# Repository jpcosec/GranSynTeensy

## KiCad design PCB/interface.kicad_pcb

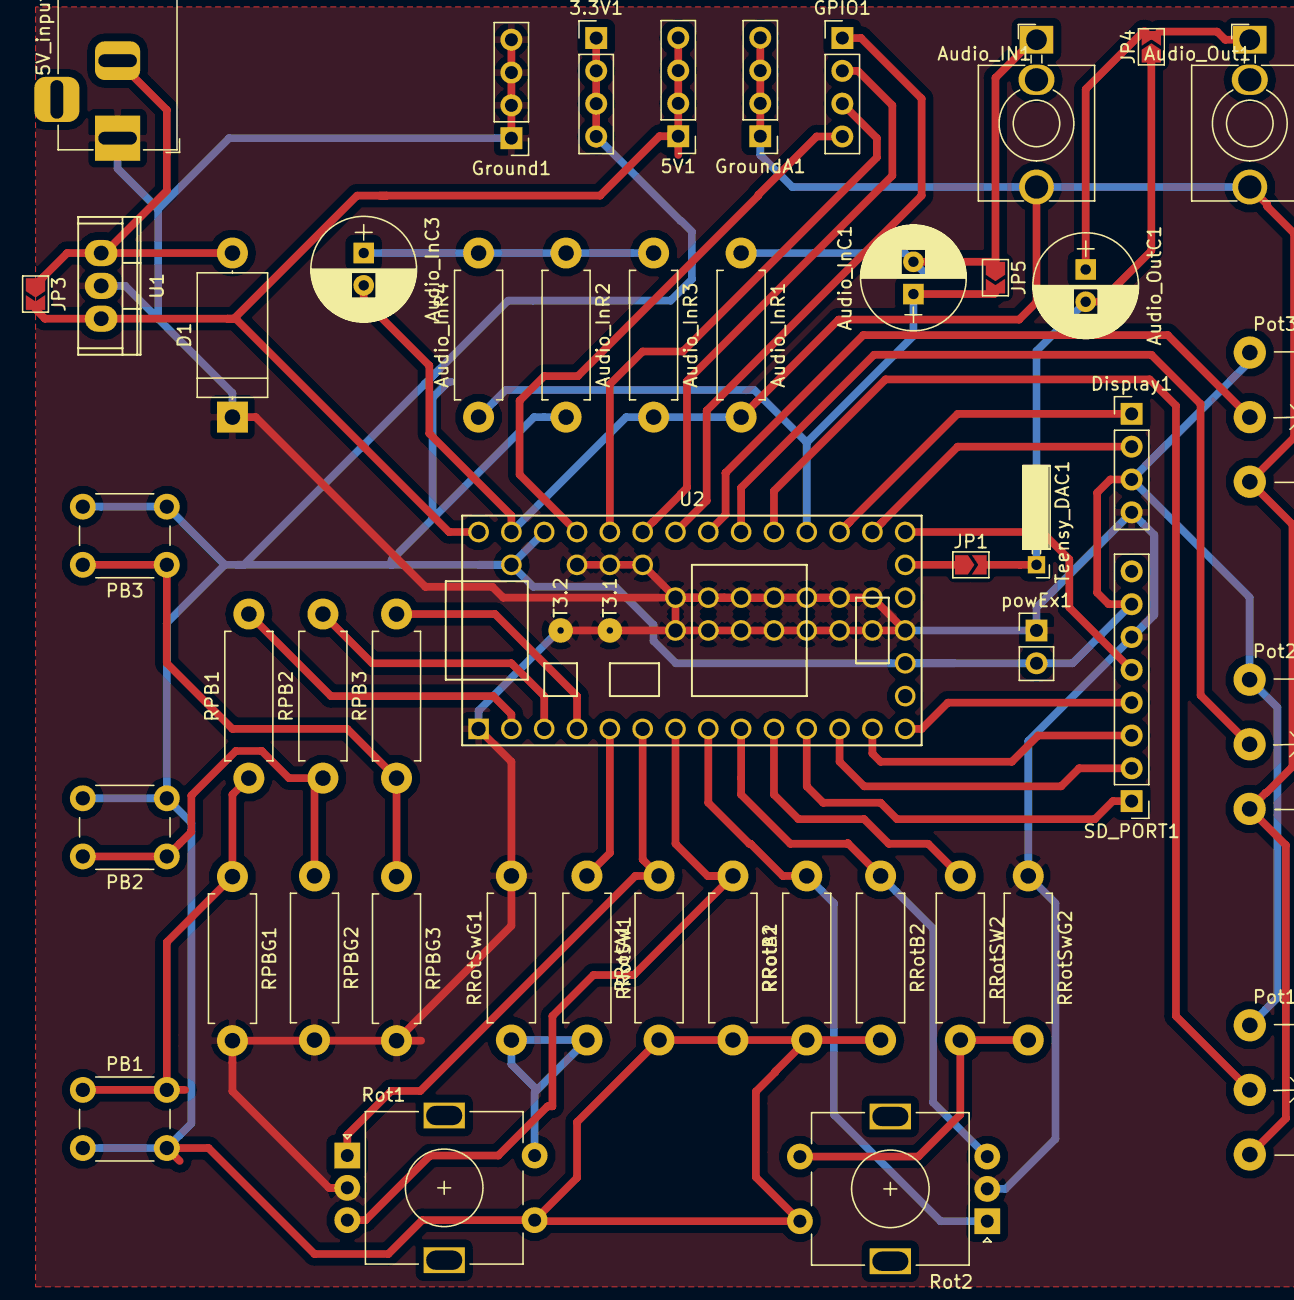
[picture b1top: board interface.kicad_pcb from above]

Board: 2 copper layers, 48 parts (0 on the bottom side), 39 nets.

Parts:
3.3V1, 5V1: Conn_01x04_Female; Pin_Header_Straight_1x04_Pitch2.54mm
5V_input1: Jack-DC; BarrelJack_Horizontal
Audio_IN1: AudioJack2_Ground; Jack_3.5mm_QingPu_WQP-PJ398SM_Vertical_CircularHoles
Audio_InC1, Audio_InC3: 10uf; CP_Radial_D8.0mm_P2.50mm
Audio_InR1, Audio_InR4: 47K; R_Axial_DIN0411_L9.9mm_D3.6mm_P12.70mm_Horizontal
Audio_InR2: 10K; R_Axial_DIN0411_L9.9mm_D3.6mm_P12.70mm_Horizontal
Audio_InR3: 2.2K; R_Axial_DIN0411_L9.9mm_D3.6mm_P12.70mm_Horizontal
Audio_Out1: AudioJack2_Ground; Jack_3.5mm_QingPu_WQP-PJ398SM_Vertical_CircularHoles
Audio_OutC1: 10uf; CP_Radial_D8.0mm_P2.50mm
D1: DIODE; D_DO-27_P12.70mm_Horizontal
Display1: Conn_01x04_Female; Pin_Header_Straight_1x04_Pitch2.54mm
GPIO1: Conn_01x04_Female; Pin_Header_Straight_1x04_Pitch2.54mm
Ground1: Conn_01x04_Female; Pin_Header_Straight_1x04_Pitch2.54mm
GroundA1: Conn_01x04_Female; Pin_Header_Straight_1x04_Pitch2.54mm
JP1, JP3, JP4, JP5: Jumper_NO_Small; SolderJumper-2_P1.3mm_Open_TrianglePad1.0x1.5mm
PB1, PB2, PB3: SW_Push; SW_PUSH_6mm_h4.3mm
Pot1, Pot2, Pot3: R_POT; Potentiometer_WirePads_largePads
RPB1, RPB2, RPB3: 220R; R_Axial_DIN0411_L9.9mm_D3.6mm_P12.70mm_Horizontal
RPBG1, RPBG2, RPBG3: 10k; R_Axial_DIN0411_L9.9mm_D3.6mm_P12.70mm_Horizontal
RRotA1, RRotA2: 10k; R_Axial_DIN0411_L9.9mm_D3.6mm_P12.70mm_Horizontal
RRotB1, RRotB2: 10k; R_Axial_DIN0411_L9.9mm_D3.6mm_P12.70mm_Horizontal
RRotSW1, RRotSW2: 220R; R_Axial_DIN0411_L9.9mm_D3.6mm_P12.70mm_Horizontal
RRotSwG1, RRotSwG2: 10k; R_Axial_DIN0411_L9.9mm_D3.6mm_P12.70mm_Horizontal
Rot1, Rot2: Rotary; RotaryEncoder_Alps_EC11E-Switch_Vertical_H20mm
SD_PORT1: Conn_01x08_Female; Pin_Header_Straight_1x08_Pitch2.54mm
Teensy_DAC1: Conn_01x01_Female; Socket_Strip_Angled_1x01_Pitch2.00mm
U1: LM7805_TO220; TO-220
U2: Teensy3.2; Teensy30_31_32_LC
powEx1: Conn_01x02_Female; Pin_Header_Straight_1x02_Pitch2.54mm

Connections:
+3V3: 3.3V1.1, 3.3V1.2, 3.3V1.3, 3.3V1.4, Audio_InR2.2, Display1.3, PB1.2, PB2.2, PB3.2, Pot1.1, Pot2.1, Pot3.1, RRotA1.1, RRotA2.1, RRotB1.2, RRotB2.2, Rot1.S1, Rot2.S2, SD_PORT1.7, U2.16, U2.31, U2.34, powEx1.2
+5V: 5V1.1, 5V1.2, 5V1.3, 5V1.4, JP3.2, U1.3, U2.33
AUDIO_IN: Audio_InC1.1, Audio_InR4.1, JP5.2, U2.23
CLK_DISP: Display1.1, U2.22
CS: SD_PORT1.2, U2.12
CSK: SD_PORT1.5, U2.20
DAC: JP1.1, U2.19
DI: SD_PORT1.3, U2.13
DIO_DISP: Display1.2, U2.21
DO: SD_PORT1.4, U2.14
GND: 5V_input1.1, D1.1, Display1.4, Ground1.1, Ground1.2, Ground1.3, Ground1.4, RPBG1.2, RPBG2.2, RPBG3.2, RRotSwG1.2, RRotSwG2.1, Rot1.C, Rot2.C, SD_PORT1.6, U1.2, U2.1, U2.17, U2.35, U2.36, U2.37, U2.38, U2.39, U2.40, U2.41, U2.42, U2.43, U2.44, U2.45, U2.46, U2.47, U2.48, U2.49, U2.50, U2.51, U2.52, powEx1.1
GNDA: Audio_IN1.T, Audio_InC3.2, Audio_InR1.2, Audio_InR3.2, Audio_Out1.T, GroundA1.1, GroundA1.2, GroundA1.3, GroundA1.4, Pot1.3, Pot2.3, Pot3.3, U2.32
GPIO1: GPIO1.1, U2.27
GPIO2: GPIO1.2, U2.28
GPIO3: GPIO1.3, U2.29
GPIO4: GPIO1.4, U2.30
unnamed: 5V_input1.2, D1.2, JP3.1, U1.1
unnamed: Audio_IN1.S, Audio_InC1.2, Audio_InR1.1, JP5.1
unnamed: Audio_InC3.1, Audio_InR2.1, Audio_InR3.1, Audio_InR4.2
unnamed: Audio_Out1.S, Audio_OutC1.1, JP4.2
unnamed: Audio_OutC1.2, JP1.2, JP4.1, Teensy_DAC1.1
unnamed: PB1.1, RPB1.1, RPBG1.1
unnamed: PB2.1, RPB2.1, RPBG2.1
unnamed: PB3.1, RPB3.1, RPBG3.1
unnamed: RRotSW1.2, RRotSwG1.1, Rot1.S2
unnamed: RRotSW2.2, RRotSwG2.2, Rot2.S1
PB_1: RPB1.2, U2.2
PB_2: RPB2.2, U2.3
PB_3: RPB3.2, U2.4
Pot1: Pot1.2, U2.24
Pot2: Pot2.2, U2.25
Pot3: Pot3.2, U2.26
Rot_CLK: RRotA1.2, Rot1.A, U2.6
Rot_CLK2: RRotA2.2, Rot2.A, U2.8
Rot_DT: RRotB1.1, Rot1.B, U2.7
Rot_DT2: RRotB2.1, Rot2.B, U2.9
Rot_SW: RRotSW1.1, U2.5
Rot_SW2: RRotSW2.1, U2.10
SD: SD_PORT1.1, U2.11

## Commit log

2019-01-02 Inicializacion
    Inicializacion PCB
2019-01-02 Code folder uploading
2019-01-02 Sube código de Teensy
